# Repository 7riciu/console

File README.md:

# 💗 Console

A Gameboy-inspired console you can play snake-game on 🎮

It's my first ever hardware project. I started from the Fallout tamagotchi tutorial and I later transformed it into something more personal (this console). I wanted to create something cute, fun and small enough to carry around.

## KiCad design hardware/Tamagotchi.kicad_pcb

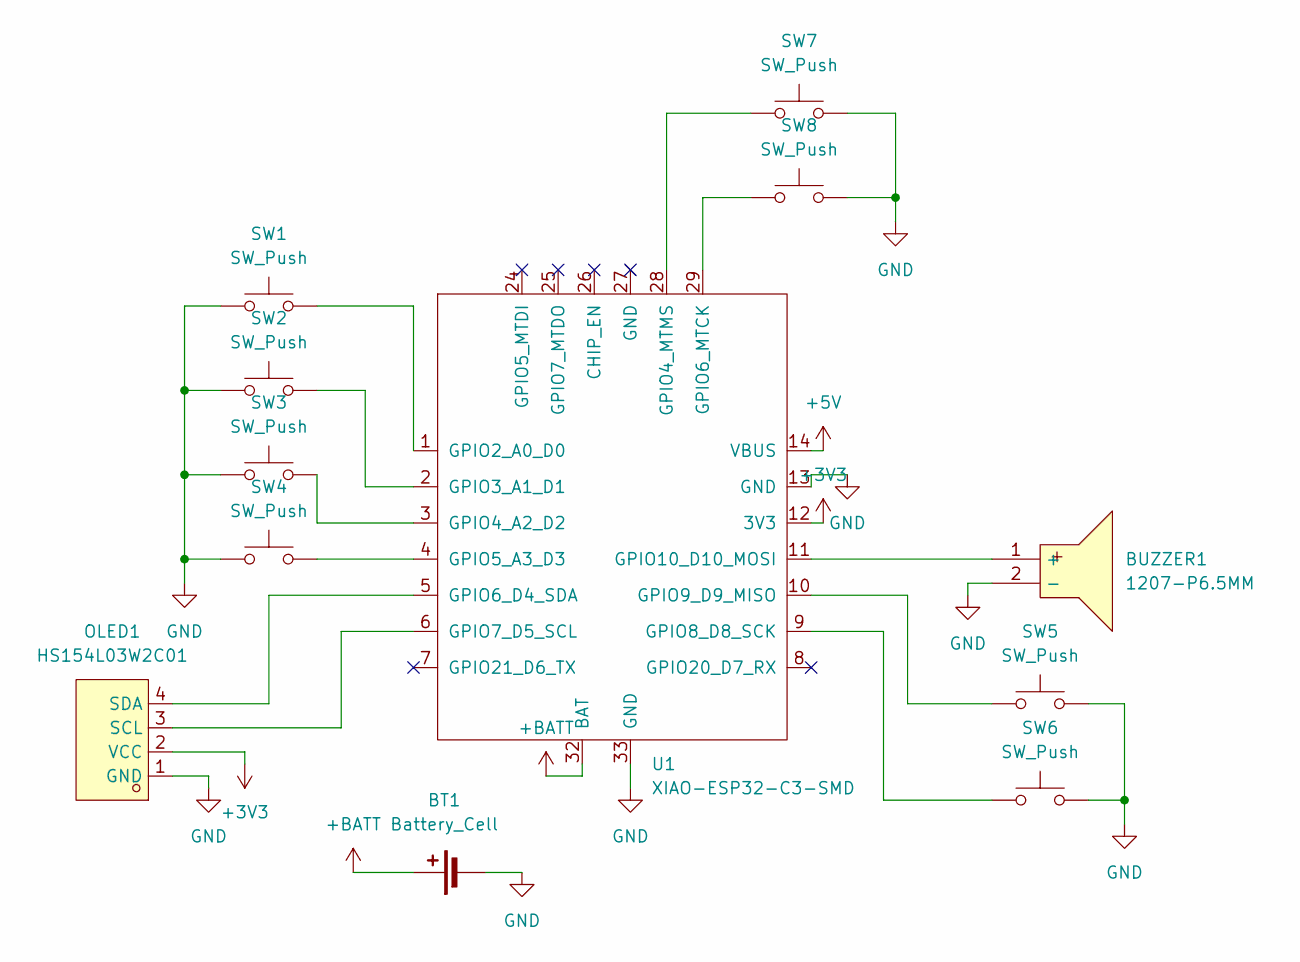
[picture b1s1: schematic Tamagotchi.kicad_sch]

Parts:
BT1: Battery_Cell; PinHeader_1x02_P2.54mm_Vertical
BUZZER1: 1207-P6.5MM; BUZ-TH_BD12.5-P6.50-D1.4; MPN 1207-P6.5MM; LCSC Part C49246964
OLED1: HS154L03W2C01; OLED-TH_-4P-L42.4-W38.0-P2.54; MPN HS154L03W2C01; LCSC Part C7465999
SW1, SW2, SW3, SW4, SW5, SW6, SW7, SW8: SW_Push; SW-TH_4P-L4.5-W4.5-P3.00-LS4.8
U1: XIAO-ESP32-C3-SMD; XIAO-ESP32-C3-DIP-SMD

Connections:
+3V3: OLED1.2 (VCC), U1.12 (3V3)
+5V: U1.14 (VBUS)
+BATT: BT1.1 (+), U1.32 (BAT)
GND: BT1.2 (-), BUZZER1.2 (-), OLED1.1 (GND), SW1.1, SW2.1, SW3.1, SW4.1, SW5.2, SW6.2, SW7.2, SW8.2, U1.13 (GND), U1.33 (GND)
unnamed: BUZZER1.1 (+), U1.11 (GPIO10_D10_MOSI)
unnamed: OLED1.3 (SCL), U1.6 (GPIO7_D5_SCL)
unnamed: OLED1.4 (SDA), U1.5 (GPIO6_D4_SDA)
unnamed: SW1.2, U1.1 (GPIO2_A0_D0)
unnamed: SW2.2, U1.2 (GPIO3_A1_D1)
unnamed: SW3.2, U1.3 (GPIO4_A2_D2)
unnamed: SW7.1, U1.28 (GPIO4_MTMS)
unnamed: SW4.2, U1.4 (GPIO5_A3_D3)
unnamed: SW8.1, U1.29 (GPIO6_MTCK)
unnamed: SW6.1, U1.9 (GPIO8_D8_SCK)
unnamed: SW5.1, U1.10 (GPIO9_D9_MISO)

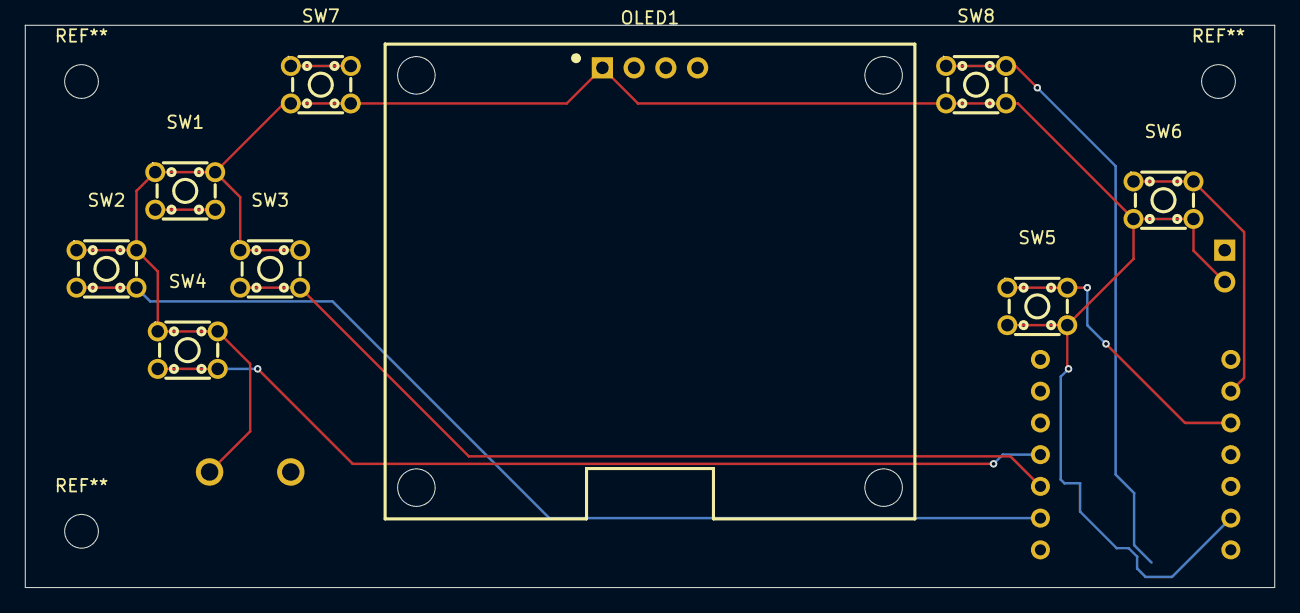
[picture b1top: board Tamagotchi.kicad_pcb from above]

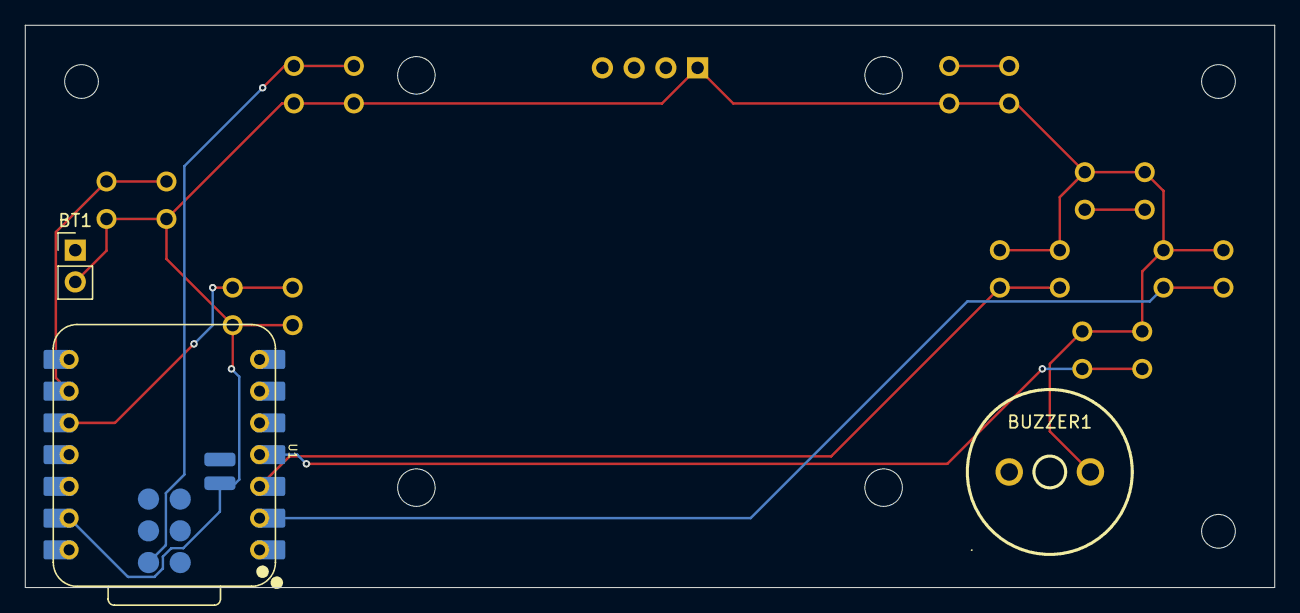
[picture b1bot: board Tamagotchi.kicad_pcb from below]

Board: 2 copper layers, 100.0 x 45.0 mm, 12 parts (3 on the bottom side), 14 nets.
